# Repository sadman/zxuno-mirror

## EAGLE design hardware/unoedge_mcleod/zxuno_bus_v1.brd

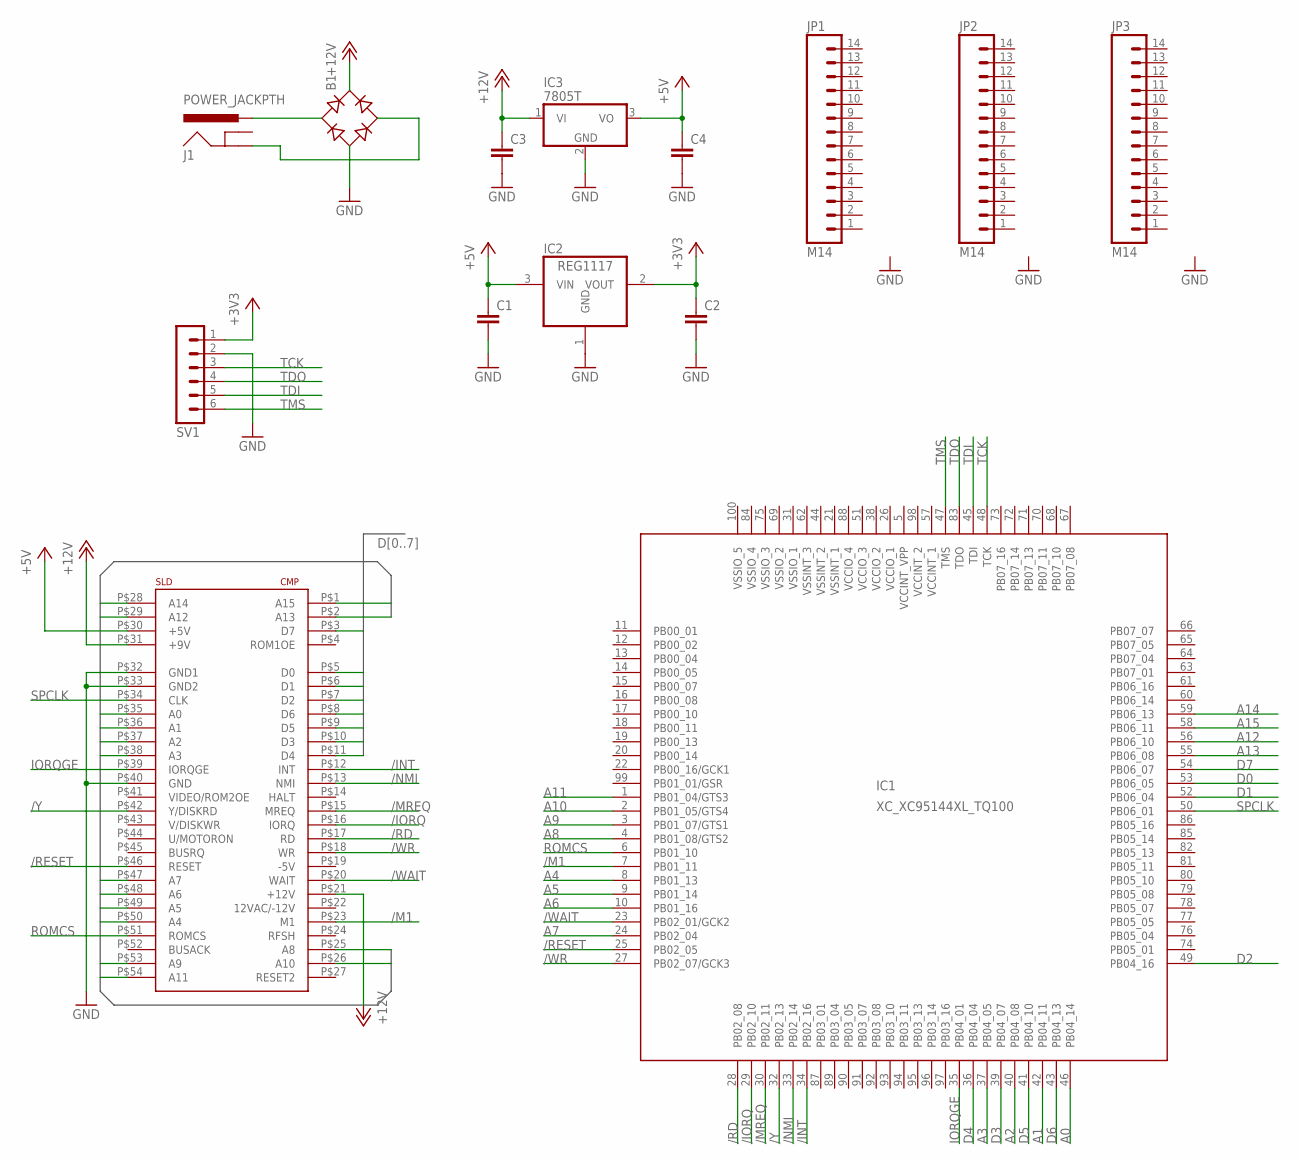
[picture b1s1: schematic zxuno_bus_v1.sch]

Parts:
B1: RB1A
C1, C2, C3, C4: C-EUC1206K; C1206K
IC1: XC_XC95144XL_TQ100; XC_XC-TQ100
IC2: REG1117; SOT223
IC3: 7805T; TO220H
J1: POWER_JACKPTH; POWER_JACK_PTH
JP1, JP2, JP3: M14; 1X14
SV1: MA06-1
U$1: CONECTOR_EDGE_LADO_SPECTRUM; CONECTOR_LADO_SPECTRUM

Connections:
+3V3: C2.1, IC1.5 (VCCINT_VPP), IC1.26 (VCCIO_1), IC1.38 (VCCIO_2), IC1.51 (VCCIO_3), IC1.57 (VCCINT_1), IC1.88 (VCCIO_4), IC1.98 (VCCINT_2), IC2.2 (VOUT), SV1.1
+5V: C1.1, C4.1, IC2.3 (VIN), IC3.3 (VO), U$1.P$30 (+5V)
+12V: B1.+, C3.1, IC3.1 (VI), U$1.P$21 (+12V), U$1.P$31 (+9V)
/INT: IC1.34 (PB02_16), U$1.P$12 (INT)
/IORQ: IC1.29 (PB02_10), U$1.P$16 (IORQ)
/M1: IC1.7 (PB01_11), U$1.P$23 (M1)
/MREQ: IC1.30 (PB02_11), U$1.P$15 (MREQ)
/NMI: IC1.33 (PB02_14), U$1.P$13 (NMI)
/RD: IC1.28 (PB02_08), U$1.P$17 (RD)
/RESET: IC1.25 (PB02_05), U$1.P$46 (RESET)
/WAIT: IC1.23 (PB02_01/GCK2), U$1.P$20 (WAIT)
/WR: IC1.27 (PB02_07/GCK3), U$1.P$18 (WR)
/Y: IC1.32 (PB02_13), U$1.P$42 (Y/DISKRD)
A0: IC1.46 (PB04_14), U$1.P$35 (A0)
A1: IC1.42 (PB04_11), U$1.P$36 (A1)
A2: IC1.40 (PB04_08), U$1.P$37 (A2)
A3: IC1.37 (PB04_05), U$1.P$38 (A3)
A4: IC1.8 (PB01_13), U$1.P$50 (A4)
A5: IC1.9 (PB01_14), U$1.P$49 (A5)
A6: IC1.10 (PB01_16), U$1.P$48 (A6)
A7: IC1.24 (PB02_04), U$1.P$47 (A7)
A8: IC1.4 (PB01_08/GTS2), U$1.P$25 (A8)
A9: IC1.3 (PB01_07/GTS1), U$1.P$53 (A9)
A10: IC1.2 (PB01_05/GTS4), U$1.P$26 (A10)
A11: IC1.1 (PB01_04/GTS3), U$1.P$54 (A11)
A12: IC1.56 (PB06_10), U$1.P$29 (A12)
A13: IC1.55 (PB06_08), U$1.P$2 (A13)
A14: IC1.59 (PB06_13), U$1.P$28 (A14)
A15: IC1.58 (PB06_11), U$1.P$1 (A15)
D0: IC1.53 (PB06_05), U$1.P$5 (D0)
D1: IC1.52 (PB06_04), U$1.P$6 (D1)
D2: IC1.49 (PB04_16), U$1.P$7 (D2)
D3: IC1.39 (PB04_07), U$1.P$10 (D3)
D4: IC1.36 (PB04_04), U$1.P$11 (D4)
D5: IC1.41 (PB04_10), U$1.P$9 (D5)
D6: IC1.43 (PB04_13), U$1.P$8 (D6)
D7: IC1.54 (PB06_07), U$1.P$3 (D7)
GND: B1.-, C1.2, C2.2, C3.2, C4.2, IC1.21 (VSSINT_1), IC1.31 (VSSIO_1), IC1.44 (VSSINT_2), IC1.62 (VSSINT_3), IC1.69 (VSSIO_2), IC1.75 (VSSIO_3), IC1.84 (VSSIO_4), IC1.100 (VSSIO_5), IC2.1 (GND), IC3.2 (GND), SV1.2, U$1.P$32 (GND1), U$1.P$33 (GND2), U$1.P$40 (GND)
IORQGE: IC1.35 (PB04_01), U$1.P$39 (IORQGE)
unnamed: B1.AC1, J1.PWR
unnamed: B1.AC2, J1.GND
ROMCS: IC1.6 (PB01_10), U$1.P$51 (ROMCS)
SPCLK: IC1.50 (PB06_01), U$1.P$34 (CLK)
TCK: IC1.48 (TCK), SV1.3
TDI: IC1.45 (TDI), SV1.5
TDO: IC1.83 (TDO), SV1.4
TMS: IC1.47 (TMS), SV1.6

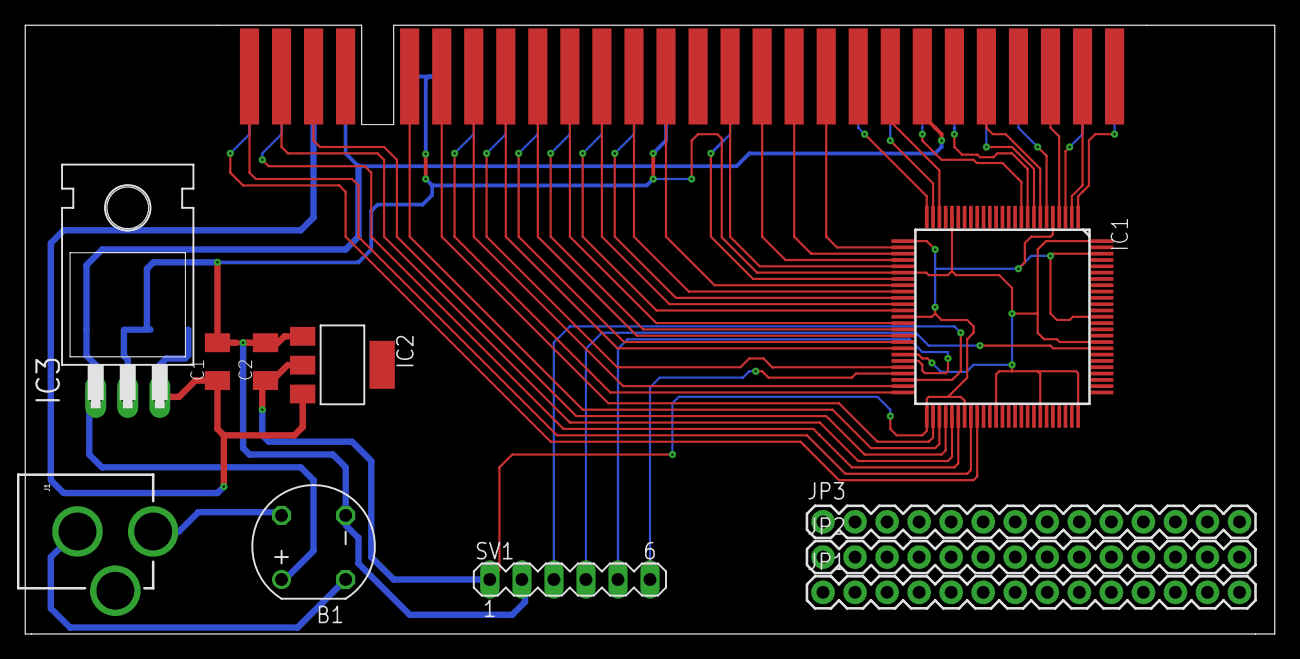
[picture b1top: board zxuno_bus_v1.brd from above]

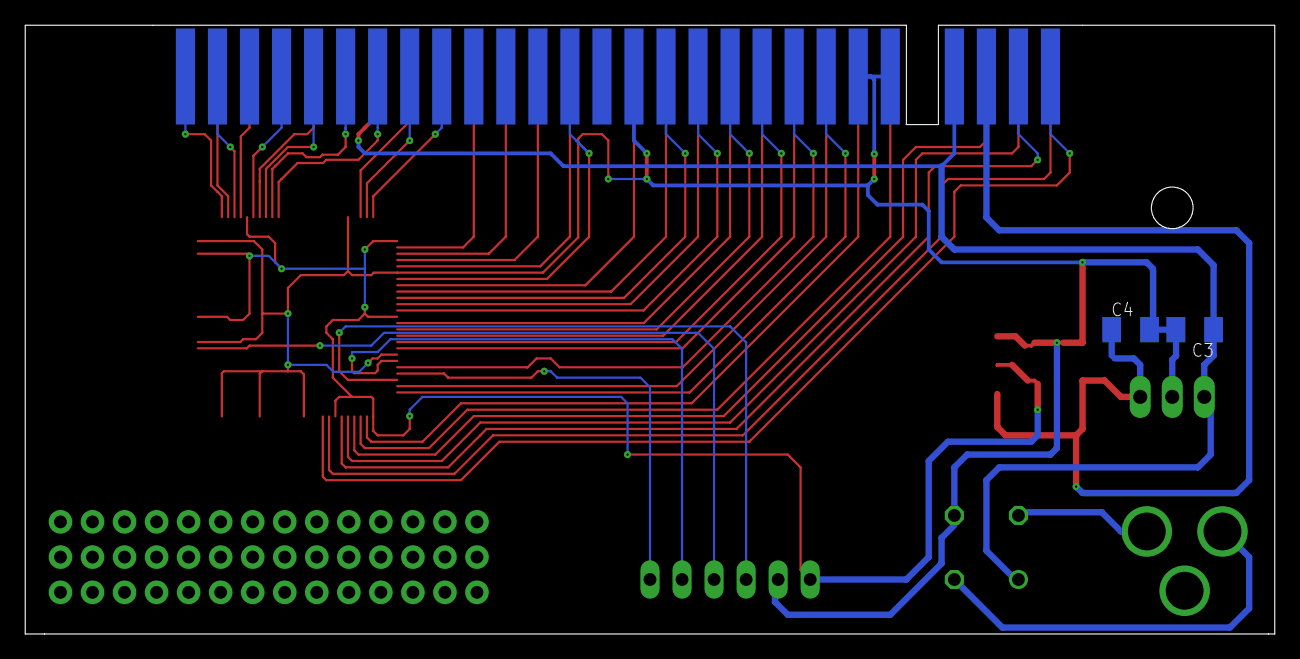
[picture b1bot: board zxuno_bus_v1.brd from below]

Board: 2 copper layers, 99.1 x 48.3 mm, 14 parts (2 on the bottom side), 47 nets.

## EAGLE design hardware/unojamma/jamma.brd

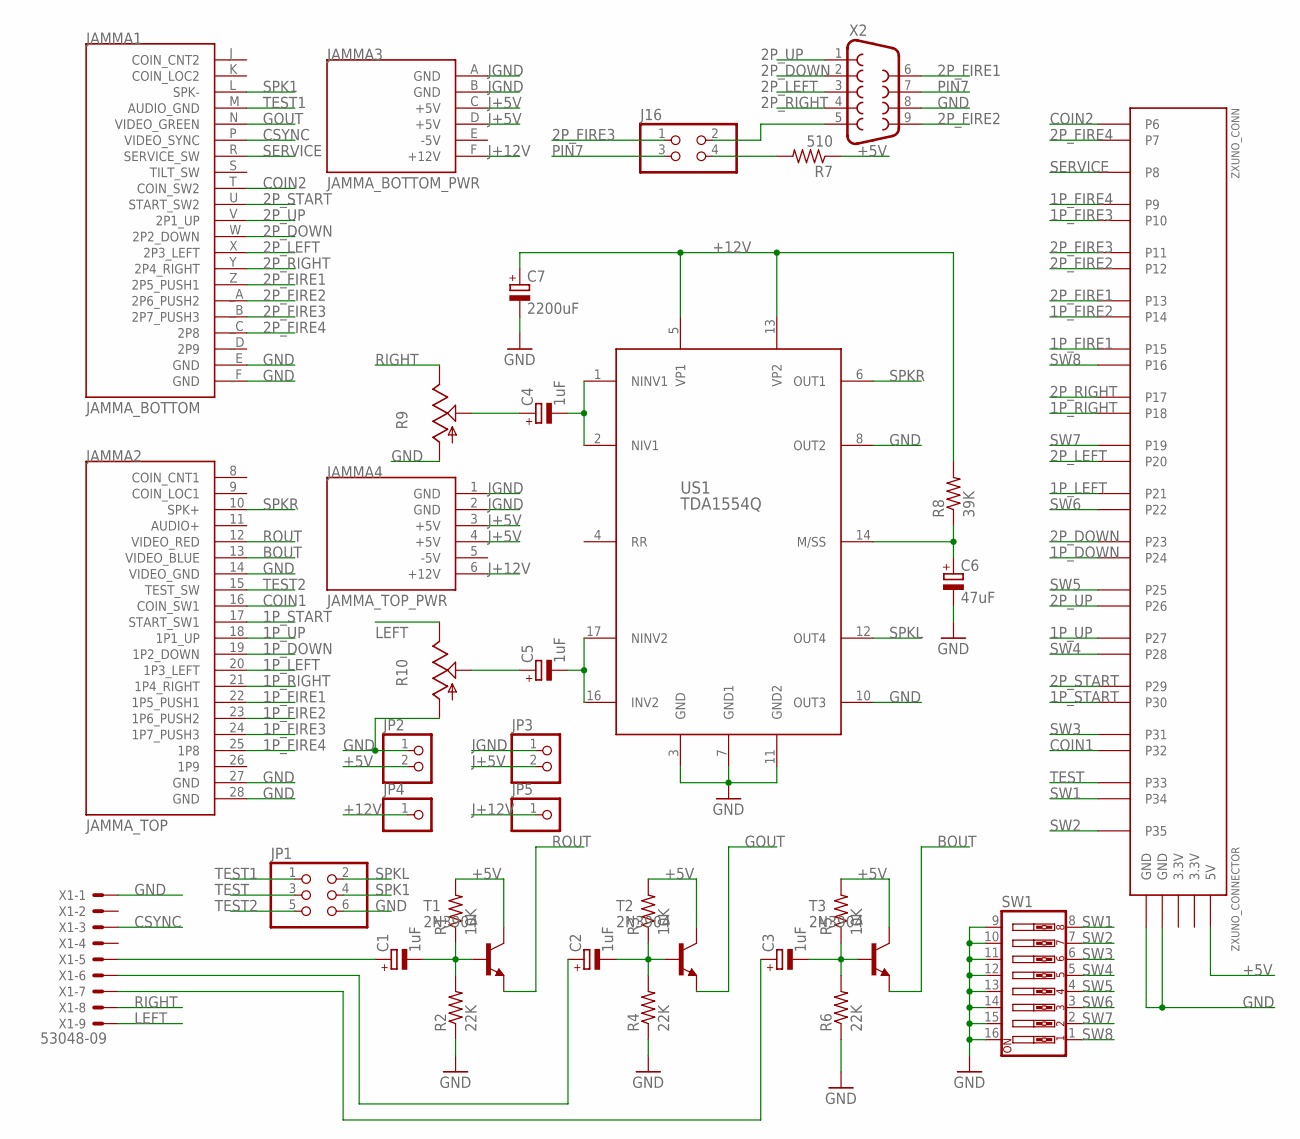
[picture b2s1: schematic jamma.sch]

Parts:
C1, C2, C3, C4, C5: 1uF; E2-5
C6: 47uF; E5-5
C7: 2200uF; E5-10,5
J16: PINHD-2X2; 2X02
JAMMA1: JAMMA_BOTTOM
JAMMA2: JAMMA_TOP
JAMMA3: JAMMA_BOTTOM_PWR
JAMMA4: JAMMA_TOP_PWR
JP1: PINHD-2X3/90; 2X03/90
JP2, JP3: PINHD-1X2; 1X02
JP4, JP5: PINHD-1X1; 1X01
R1, R3, R5: 10K; 0204/7
R2, R4, R6: 22K; 0204/7
R7: 510; 0204/7
R8: 39K; 0204/7
R9, R10: TRIM_US-CA6V; CA6V
SW1: SW_DIP-8; EDG-08
T1, T2, T3: 2N3904; TO92
US1: TDA1554Q; SOT243-1
X1: 53048-09
X2: DB9MALE; DB9_MALE
ZXUNO_CONN: ZXUNO_CONNECTOR

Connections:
1P_DOWN: JAMMA2.19 (1P2_DOWN), ZXUNO_CONN.P24
1P_FIRE1: JAMMA2.22 (1P5_PUSH1), ZXUNO_CONN.P15
1P_FIRE2: JAMMA2.23 (1P6_PUSH2), ZXUNO_CONN.P14
1P_FIRE3: JAMMA2.24 (1P7_PUSH3), ZXUNO_CONN.P10
1P_FIRE4: JAMMA2.25 (1P8), ZXUNO_CONN.P9
1P_LEFT: JAMMA2.20 (1P3_LEFT), ZXUNO_CONN.P21
1P_RIGHT: JAMMA2.21 (1P4_RIGHT), ZXUNO_CONN.P18
1P_START: JAMMA2.17 (START_SW1), ZXUNO_CONN.P30
1P_UP: JAMMA2.18 (1P1_UP), ZXUNO_CONN.P27
2P_DOWN: JAMMA1.W (2P2_DOWN), X2.2, ZXUNO_CONN.P23
2P_FIRE1: JAMMA1.Z (2P5_PUSH1), X2.6, ZXUNO_CONN.P13
2P_FIRE2: JAMMA1._A (2P6_PUSH2), X2.9, ZXUNO_CONN.P12
2P_FIRE3: J16.1, JAMMA1._B (2P7_PUSH3), ZXUNO_CONN.P11
2P_FIRE4: JAMMA1._C (2P8), ZXUNO_CONN.P7
2P_LEFT: JAMMA1.X (2P3_LEFT), X2.3, ZXUNO_CONN.P20
2P_RIGHT: JAMMA1.Y (2P4_RIGHT), X2.4, ZXUNO_CONN.P17
2P_START: JAMMA1.U (START_SW2), ZXUNO_CONN.P29
2P_UP: JAMMA1.V (2P1_UP), X2.1, ZXUNO_CONN.P26
3.3V: ZXUNO_CONN.3.3V@1 (3.3V), ZXUNO_CONN.3.3V@2 (3.3V)
+5V: JP2.2, R1.2, R3.2, R5.2, R7.1, T1.1 (C), T2.1 (C), T3.1 (C), ZXUNO_CONN.5V
+12V: C7.+, JP4.1, R8.2, US1.5 (VP1), US1.13 (VP2)
-5V: JAMMA3.E (-5V), JAMMA4.5 (-5V)
BIN: C3.+, X1.3
BOUT: JAMMA2.13 (VIDEO_BLUE), T3.3 (E)
COIN1: JAMMA2.16 (COIN_SW1), ZXUNO_CONN.P32
COIN2: JAMMA1.T (COIN_SW2), ZXUNO_CONN.P6
CSYNC: JAMMA1.P (VIDEO_SYNC), X1.7
GIN: C2.+, X1.4
GND: C6.-, C7.-, JAMMA1._E (GND), JAMMA1._F (GND), JAMMA2.14 (VIDEO_GND), JAMMA2.27 (GND), JAMMA2.28 (GND), JP1.6, JP2.1, R2.1, R4.1, R6.1, R9.A, R10.A, SW1.9, SW1.10, SW1.11, SW1.12, SW1.13, SW1.14, SW1.15, SW1.16, US1.3 (GND), US1.7 (GND1), US1.8 (OUT2), US1.10 (OUT3), US1.11 (GND2), X1.9, X2.8, ZXUNO_CONN.GND@1 (GND), ZXUNO_CONN.GND@2 (GND)
GOUT: JAMMA1.N (VIDEO_GREEN), T2.3 (E)
J+5V: JAMMA3.C (+5V), JAMMA3.D (+5V), JAMMA4.3 (+5V), JAMMA4.4 (+5V), JP3.2
J+12V: JAMMA3.F (+12V), JAMMA4.6 (+12V), JP5.1
JGND: JAMMA3.A (GND), JAMMA3.B (GND), JAMMA4.1 (GND), JAMMA4.2 (GND), JP3.1
LEFT: R10.E, X1.1
unnamed: C4.-, US1.1 (NINV1), US1.2 (NIV1)
unnamed: C5.-, US1.16 (INV2), US1.17 (NINV2)
unnamed: C5.+, R10.S
unnamed: C1.-, R1.1, R2.2, T1.2 (B)
unnamed: J16.2, X2.5
unnamed: C6.+, R8.1, US1.14 (M/SS)
unnamed: C3.-, R5.1, R6.2, T3.2 (B)
unnamed: C4.+, R9.S
unnamed: C2.-, R3.1, R4.2, T2.2 (B)
unnamed: J16.4, R7.2
PIN7: J16.3, X2.7
RIGHT: R9.E, X1.2
RIN: C1.+, X1.5
ROUT: JAMMA2.12 (VIDEO_RED), T1.3 (E)
SERVICE: JAMMA1.R (SERVICE_SW), ZXUNO_CONN.P8
SPK1: JAMMA1.L (SPK-), JP1.4
SPKL: JP1.2, US1.12 (OUT4)
SPKR: JAMMA2.10 (SPK+), US1.6 (OUT1)
SW1: SW1.8, ZXUNO_CONN.P34
SW2: SW1.7, ZXUNO_CONN.P35
SW3: SW1.6, ZXUNO_CONN.P31
SW4: SW1.5, ZXUNO_CONN.P28
SW5: SW1.4, ZXUNO_CONN.P25
SW6: SW1.3, ZXUNO_CONN.P22
SW7: SW1.2, ZXUNO_CONN.P19
SW8: SW1.1, ZXUNO_CONN.P16
TEST: JP1.3, ZXUNO_CONN.P33
TEST1: JAMMA1.M (AUDIO_GND), JP1.1
TEST2: JAMMA2.15 (TEST_SW), JP1.5

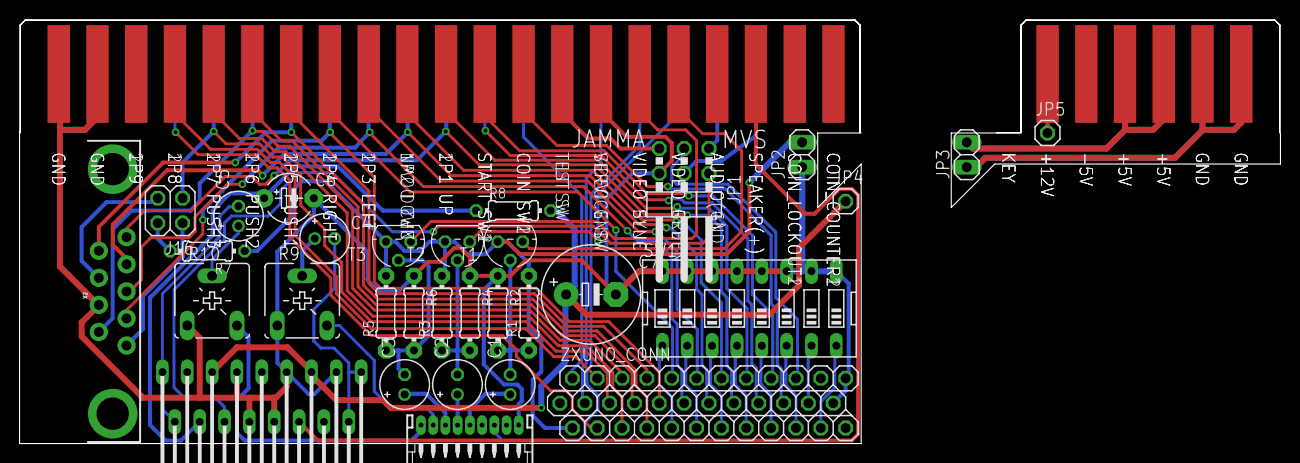
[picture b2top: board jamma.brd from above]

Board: 2 copper layers, 128.9 x 43.3 mm, 35 parts (0 on the bottom side), 63 nets.

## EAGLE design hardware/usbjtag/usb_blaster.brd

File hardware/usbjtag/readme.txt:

Schematics and firmware source code here:
http://sa89a.net/mp.cgi/ele/ub.htm

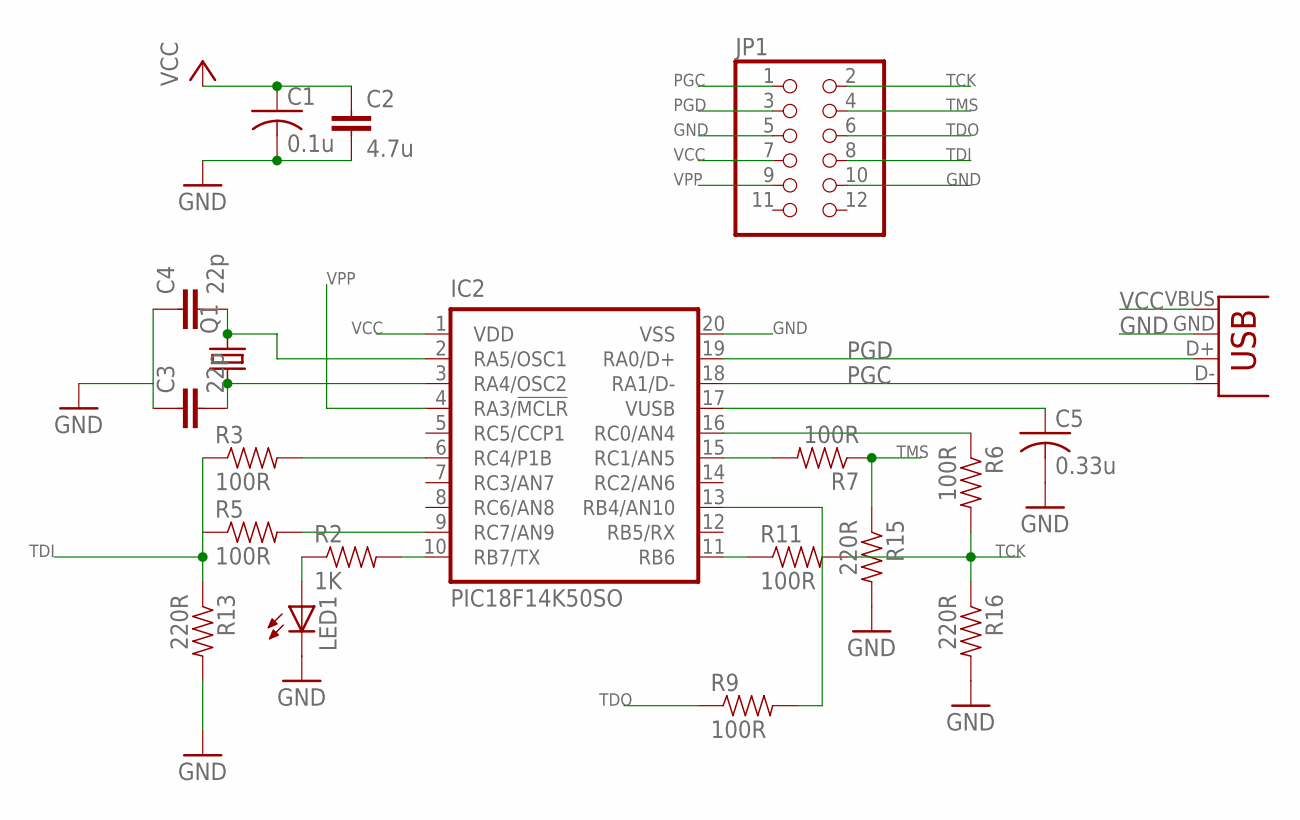
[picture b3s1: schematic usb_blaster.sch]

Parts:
C1: 0.1u; C0603K
C2: 4.7u; 0805
C3, C4: 22p; 0805
C5: 0.33u; C0603K
IC2: PIC18F14K50SO; SO20
JP1: PINHD-2X6; 2X06
LED1: LEDCHIP-LED0805; CHIP-LED0805
Q1: CRYSTALHC49UP; HC49UP
R2: 1K; 0805
R3, R5, R6, R7, R9, R11: 100R; 0805
R13, R15, R16: 220R; 0805
X2: USB-A-H

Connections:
GND: C1.2, C2.2, C3.1, C4.1, C5.2, IC2.20 (VSS), JP1.5, JP1.10, LED1.C, R13.2, R15.2, R16.2, X2.GND (VBUS)
unnamed: C4.2, IC2.2 (RA5/OSC1), Q1.2
unnamed: IC2.15 (RC1/AN5), R7.2
unnamed: C3.2, IC2.3 (RA4/OSC2), Q1.1
unnamed: IC2.16 (RC0/AN4), R6.1
unnamed: IC2.13 (RB4/AN10), R9.2
unnamed: IC2.6 (RC4/P1B), R3.2
unnamed: C5.1, IC2.17 (VUSB)
unnamed: IC2.9 (RC7/AN9), R5.2
unnamed: IC2.10 (RB7/TX), R2.2
unnamed: LED1.A, R2.1
unnamed: IC2.11 (RB6), R11.1
PGC: IC2.18 (RA1/D-), JP1.1, X2.D- (D+)
PGD: IC2.19 (RA0/D+), JP1.3, X2.D+ (D-)
TCK: JP1.2, R6.2, R11.2, R16.1
TDI: JP1.8, R3.1, R5.1, R13.1
TDO: JP1.6, R9.1
TMS: JP1.4, R7.1, R15.1
VCC: C1.1, C2.1, IC2.1 (VDD), JP1.7, X2.VBUS (GND)
VPP: IC2.4 (RA3/!MCLR!), JP1.9

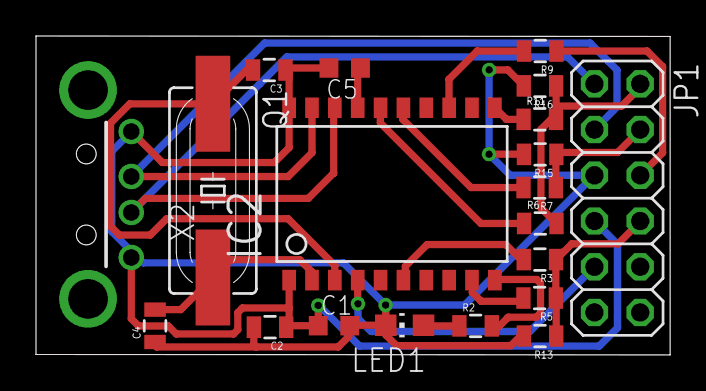
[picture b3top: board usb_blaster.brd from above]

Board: 2 copper layers, 35.2 x 17.7 mm, 20 parts (0 on the bottom side), 20 nets.

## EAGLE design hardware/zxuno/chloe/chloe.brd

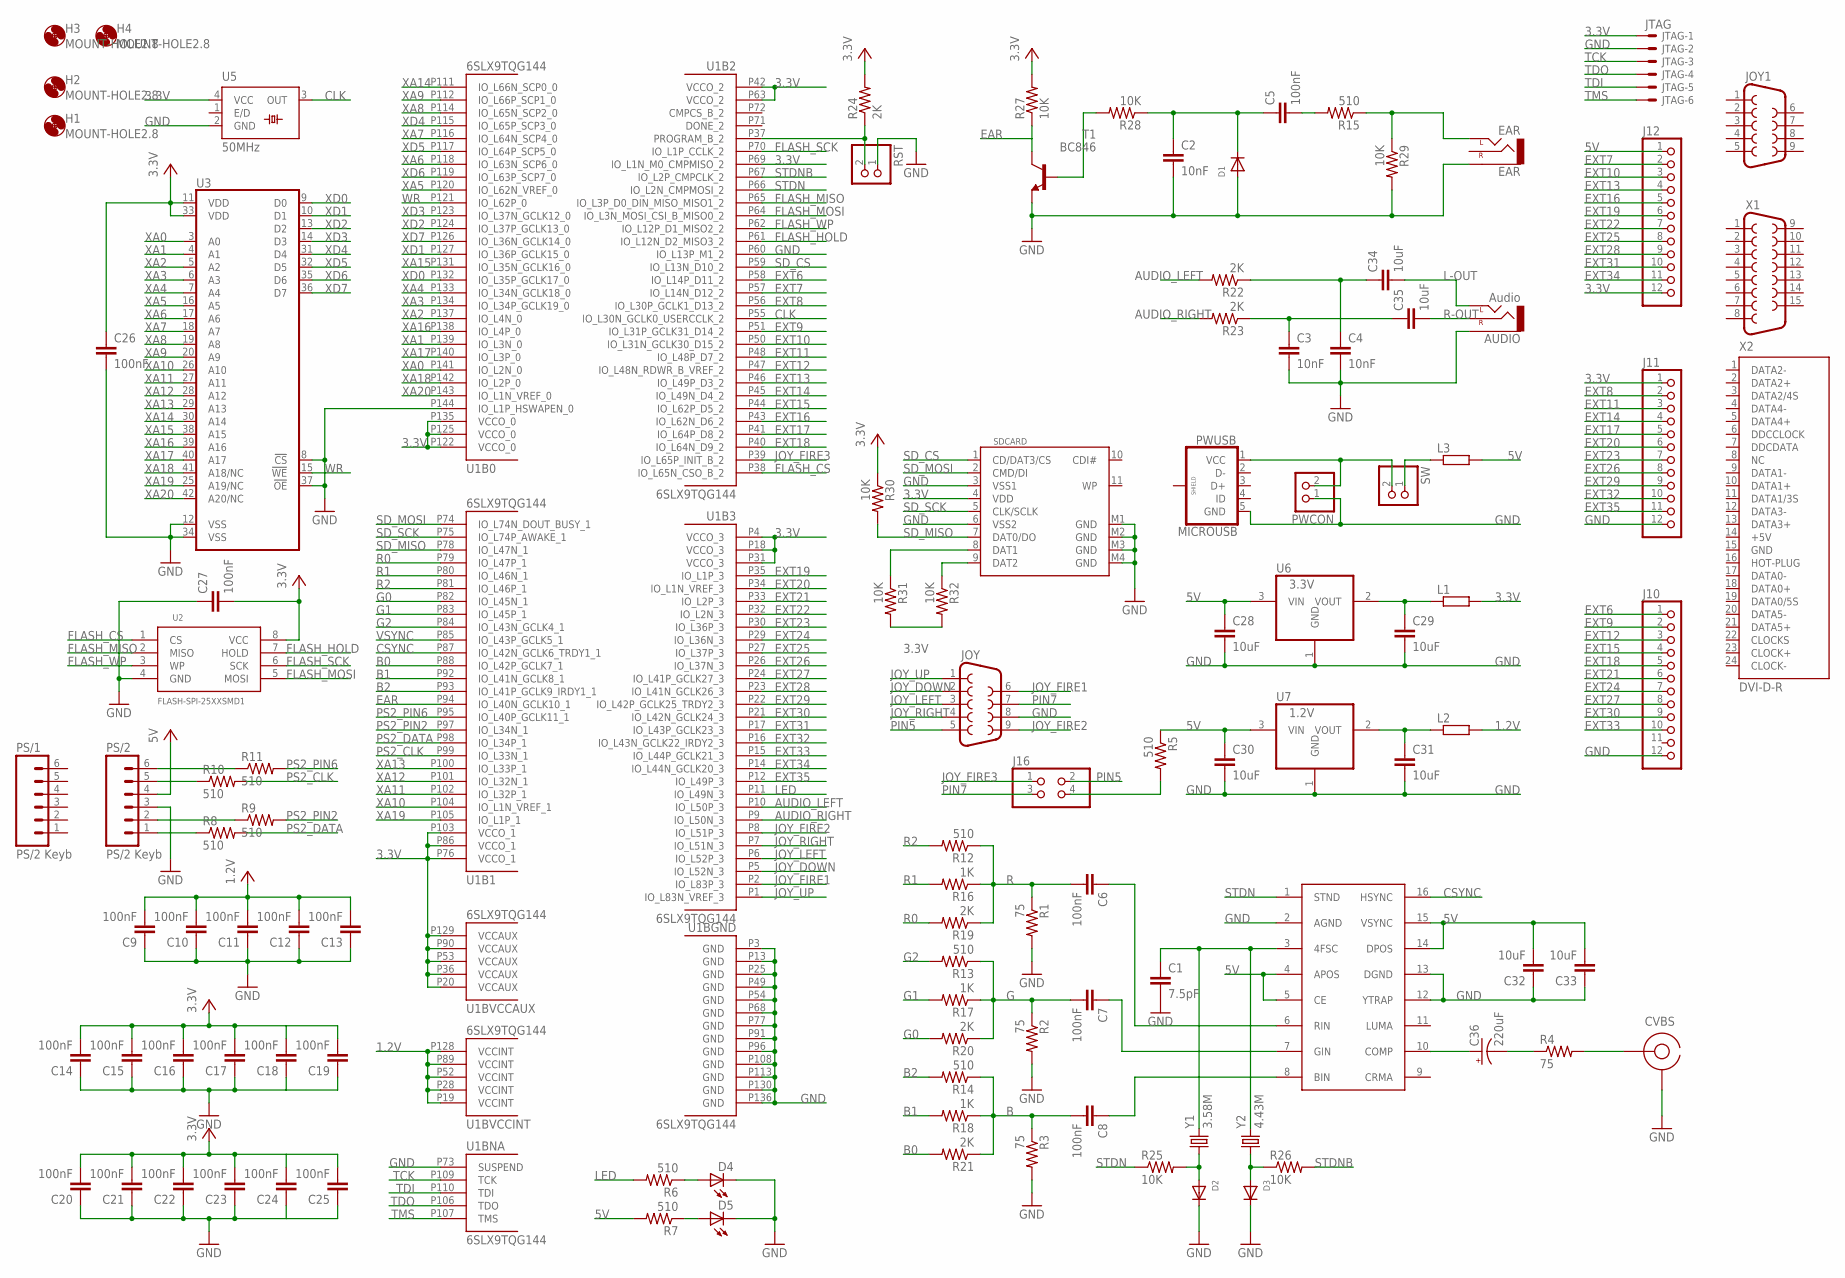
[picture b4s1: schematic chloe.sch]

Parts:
AUDIO: Audio; AUDIO-JACK
C1: 7.5pF; C0805
C2, C3, C4: 10nF; C0805
C5, C6, C7, C8, C9, C10, C11, C12, C13, C14, C15, C16, C17, C18, C19, C20, C21, C22, C23, C24, C25, C26, C27: 100nF; C0603
C28, C29, C30, C31, C32, C33, C34, C35: 10uF; C0805
C36: 220uF; 153CLV-0605
CVBS: RCA
D1, D2, D3: DIODESOD-323F; SOD-323F
D4, D5: LEDCHIP-LED0805; CHIP-LED0805
EAR: EAR; AUDIO-JACK
H1, H2, H3, H4: MOUNT-HOLE2.8; 2,8
J10, J11, J12: PINHD-1X12; 1X12
J16: PINHD-2X2; 2X02
JOY, JOY1: DB9MALE; DB9_MALE
JTAG: JTAG; 53047-06
L1, L2, L3: R-EU_M0805; M0805
PS/1, PS/2: PS/2 Keyb; DINC/MIN_TM/6_1PRIMARY
PWCON: PINHD-1X2; 1X02
PWUSB: MICROUSB; MICRO_USB_1PRIMARY
R1, R2, R3, R4: 75; M0805
R5, R6, R7, R8, R9, R10, R11, R12, R13, R14, R15: 510; M0805
R16, R17, R18: 1K; M0805
R19, R20, R21, R22, R23, R24: 2K; M0805
R25, R26, R27, R28, R29, R30, R31, R32: 10K; M0805
RST: PINHD-1X2; 1X02
SDCARD: SDCARD; SDCMF-10915W010
SW: PINHD-1X2; 1X02
T1: BC846; SOT23
U1: 6SLX9TQG144; TQ144
U2: FLASH-SPI-25XXSMD1; SO08-EIAJ
U3: ISSI_SRAM_8BIT; TSOP44-II
U4: AD724; SO16W
U5: 50MHz; SM/OSC_1PRIMARY
U6: 3.3V; SOT223
U7: 1.2V; SOT223
X1: F15HDH; HDF15H
X2: DVI-D-R
Y1: 3.58M; HC49UP
Y2: 4.43M; HC49UP

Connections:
1.2V: C9.2, C10.2, C11.2, C12.2, C13.2, L2.2, U1.P19 (VCCINT), U1.P28 (VCCINT), U1.P52 (VCCINT), U1.P89 (VCCINT), U1.P128 (VCCINT)
3.3V: C14.2, C15.2, C16.2, C17.2, C18.2, C19.2, C20.2, C21.2, C22.2, C23.2, C24.2, C25.2, C26.1, C27.2, J11.1, J12.12, JTAG.1, L1.2, R24.2, R27.2, R30.1, R31.2, R32.2, SDCARD.4 (VDD), U1.P4 (VCCO_3), U1.P18 (VCCO_3), U1.P20 (VCCAUX), U1.P31 (VCCO_3), U1.P36 (VCCAUX), U1.P42 (VCCO_2), U1.P53 (VCCAUX), U1.P63 (VCCO_2), U1.P69 (IO_L1N_M0_CMPMISO_2), U1.P76 (VCCO_1), U1.P86 (VCCO_1), U1.P90 (VCCAUX), U1.P103 (VCCO_1), U1.P122 (VCCO_0), U1.P125 (VCCO_0), U1.P129 (VCCAUX), U1.P135 (VCCO_0), U2.8 (VCC), U3.11 (VDD), U3.33 (VDD), U5.4 (VCC)
5V: C28.1, C30.1, C32.2, C33.2, J12.1, L3.2, PS/2.4, R5.1, R7.2, U4.4 (APOS), U4.5 (CE), U4.14 (DPOS), U4.15 (VSYNC), U6.3 (VIN), U7.3 (VIN)
+5V: X2.14 (+5V)
AUDIO_LEFT: R22.2, U1.P10 (IO_L50P_3)
AUDIO_RIGHT: R23.2, U1.P9 (IO_L50N_3)
B: C8.2, R3.1, R14.1, R18.1, R21.1
B0: R21.2, U1.P88 (IO_L42P_GCLK7_1)
B1: R18.2, U1.P92 (IO_L41N_GCLK8_1)
B2: R14.2, U1.P93 (IO_L41P_GCLK9_IRDY1_1)
CLK: U1.P55 (IO_L30N_GCLK0_USERCCLK_2), U5.3 (OUT)
CSYNC: U1.P87 (IO_L42N_GCLK6_TRDY1_1), U4.16 (HSYNC)
EAR: R27.1, T1.3 (C), U1.P94 (IO_L40N_GCLK10_1)
EXT6: J10.1, U1.P58 (IO_L14P_D11_2)
EXT7: J12.2, U1.P57 (IO_L14N_D12_2)
EXT8: J11.2, U1.P56 (IO_L30P_GCLK1_D13_2)
EXT9: J10.2, U1.P51 (IO_L31P_GCLK31_D14_2)
EXT10: J12.3, U1.P50 (IO_L31N_GCLK30_D15_2)
EXT11: J11.3, U1.P48 (IO_L48P_D7_2)
EXT12: J10.3, U1.P47 (IO_L48N_RDWR_B_VREF_2)
EXT13: J12.4, U1.P46 (IO_L49P_D3_2)
EXT14: J11.4, U1.P45 (IO_L49N_D4_2)
EXT15: J10.4, U1.P44 (IO_L62P_D5_2)
EXT16: J12.5, U1.P43 (IO_L62N_D6_2)
EXT17: J11.5, U1.P41 (IO_L64P_D8_2)
EXT18: J10.5, U1.P40 (IO_L64N_D9_2)
EXT19: J12.6, U1.P35 (IO_L1P_3)
EXT20: J11.6, U1.P34 (IO_L1N_VREF_3)
EXT21: J10.6, U1.P33 (IO_L2P_3)
EXT22: J12.7, U1.P32 (IO_L2N_3)
EXT23: J11.7, U1.P30 (IO_L36P_3)
EXT24: J10.7, U1.P29 (IO_L36N_3)
EXT25: J12.8, U1.P27 (IO_L37P_3)
EXT26: J11.8, U1.P26 (IO_L37N_3)
EXT27: J10.8, U1.P24 (IO_L41P_GCLK27_3)
EXT28: J12.9, U1.P23 (IO_L41N_GCLK26_3)
EXT29: J11.9, U1.P22 (IO_L42P_GCLK25_TRDY2_3)
EXT30: J10.9, U1.P21 (IO_L42N_GCLK24_3)
EXT31: J12.10, U1.P17 (IO_L43P_GCLK23_3)
EXT32: J11.10, U1.P16 (IO_L43N_GCLK22_IRDY2_3)
EXT33: J10.10, U1.P15 (IO_L44P_GCLK21_3)
EXT34: J12.11, U1.P14 (IO_L44N_GCLK20_3)
EXT35: J11.11, U1.P12 (IO_L49P_3)
FLASH_CS: U1.P38 (IO_L65N_CSO_B_2), U2.1 (CS)
FLASH_HOLD: U1.P61 (IO_L12N_D2_MISO3_2), U2.7 (HOLD)
FLASH_MISO: U1.P65 (IO_L3P_D0_DIN_MISO_MISO1_2), U2.2 (MISO)
FLASH_MOSI: U1.P64 (IO_L3N_MOSI_CSI_B_MISO0_2), U2.5 (MOSI)
FLASH_SCK: U1.P70 (IO_L1P_CCLK_2), U2.6 (SCK)
FLASH_WP: U1.P62 (IO_L12P_D1_MISO2_2), U2.3 (WP)
G: C7.2, R2.1, R13.1, R17.1, R20.1
G0: R20.2, U1.P82 (IO_L45N_1)
G1: R17.2, U1.P83 (IO_L45P_1)
G2: R13.2, U1.P84 (IO_L43N_GCLK4_1)
GND: AUDIO.SLEEVE, C1.2, C2.2, C3.2, C4.2, C9.1, C10.1, C11.1, C12.1, C13.1, C14.1, C15.1, C16.1, C17.1, C18.1, C19.1, C20.1, C21.1, C22.1, C23.1, C24.1, C25.1, C26.2, C27.1, C28.2, C29.2, C30.2, C31.2, C32.1, C33.1, CVBS.GND, D1.A, D2.C, D3.C, D4.C, D5.C, EAR.SLEEVE, J10.12, J11.12, JOY.8, JTAG.2, PS/2.3, PWCON.1, PWUSB.5 (GND), R1.2, R2.2, R3.2, R29.2, RST.1, SDCARD.3 (VSS1), SDCARD.6 (VSS2), SDCARD.M1 (GND), SDCARD.M2 (GND), SDCARD.M3 (GND), SDCARD.M4 (GND), T1.2 (E), U1.P3 (GND), U1.P13 (GND), U1.P25 (GND), U1.P49 (GND), U1.P54 (GND), U1.P60 (IO_L13P_M1_2), U1.P68 (GND), U1.P73 (SUSPEND), U1.P77 (GND), U1.P91 (GND), U1.P96 (GND), U1.P108 (GND), U1.P113 (GND), U1.P130 (GND), U1.P136 (GND), U1.P144 (IO_L1P_HSWAPEN_0), U2.4 (GND), U3.8 (!CS), U3.12 (VSS), U3.34 (VSS), U3.37 (!OE), U4.2 (AGND), U4.12 (YTRAP), U4.13 (DGND), U5.2 (GND), U6.1 (GND), U7.1 (GND), X2.15 (GND)
JOY_DOWN: JOY.2, U1.P5 (IO_L52N_3)
JOY_FIRE1: JOY.6, U1.P2 (IO_L83P_3)
JOY_FIRE2: JOY.9, U1.P8 (IO_L51P_3)
JOY_FIRE3: J16.1, U1.P39 (IO_L65P_INIT_B_2)
JOY_LEFT: JOY.3, U1.P6 (IO_L52P_3)
JOY_RIGHT: JOY.4, U1.P7 (IO_L51N_3)
JOY_UP: JOY.1, U1.P1 (IO_L83N_VREF_3)
L-OUT: AUDIO.TIP (LEFT), C34.2
LED: R6.2, U1.P11 (IO_L49N_3)
unnamed: PS/2.6, R11.1
unnamed: PS/2.5, R10.1
unnamed: PS/2.2, R9.1
unnamed: PS/2.1, R8.1
unnamed: R24.1, RST.2, U1.P37 (PROGRAM_B_2)
unnamed: R28.2, T1.1 (B)
unnamed: C2.1, C5.1, D1.C, R28.1
unnamed: C5.2, R15.2
unnamed: EAR.TIP (LEFT), R15.1, R29.1
unnamed: C3.1, C35.1, R23.1
unnamed: C4.1, C34.1, R22.1
unnamed: PWCON.2, PWUSB.1 (VCC), SW.2
unnamed: L3.1, SW.1
unnamed: C29.1, L1.1, U6.2 (VOUT)
unnamed: J16.4, R5.2
unnamed: C31.1, L2.1, U7.2 (VOUT)
unnamed: R31.1, SDCARD.8 (DAT1)
unnamed: C8.1, U4.8 (BIN)
unnamed: R32.1, SDCARD.9 (DAT2)
unnamed: C7.1, U4.7 (GIN)
unnamed: C6.1, U4.6 (RIN)
unnamed: C1.1, U4.3 (4FSC), Y1.2, Y2.2
unnamed: D3.A, R26.1, Y2.1
unnamed: D2.A, R25.2, Y1.1
unnamed: C36.+, U4.10 (COMP)
unnamed: C36.-, R4.1
unnamed: CVBS.SIG, R4.2
unnamed: D4.A, R6.1
unnamed: D5.A, R7.1
PIN5: J16.2, JOY.5
PIN7: J16.3, JOY.7
PS2_CLK: R10.2, U1.P99 (IO_L33N_1)
PS2_DATA: R8.2, U1.P98 (IO_L34P_1)
PS2_PIN2: R9.2, U1.P97 (IO_L34N_1)
PS2_PIN6: R11.2, U1.P95 (IO_L40P_GCLK11_1)
R: C6.2, R1.1, R12.1, R16.1, R19.1
R0: R19.2, U1.P79 (IO_L47P_1)
R1: R16.2, U1.P80 (IO_L46N_1)
R2: R12.2, U1.P81 (IO_L46P_1)
R-OUT: AUDIO.RING (RIGHT), C35.2
SD_CS: SDCARD.1 (CD/DAT3/CS), U1.P59 (IO_L13N_D10_2)
SD_MISO: R30.2, SDCARD.7 (DAT0/DO), U1.P78 (IO_L47N_1)
SD_MOSI: SDCARD.2 (CMD/DI), U1.P74 (IO_L74N_DOUT_BUSY_1)
SD_SCK: SDCARD.5 (CLK/SCLK), U1.P75 (IO_L74P_AWAKE_1)
STDN: R25.1, U1.P66 (IO_L2N_CMPMOSI_2), U4.1 (STND)
STDNB: R26.2, U1.P67 (IO_L2P_CMPCLK_2)
TCK: JTAG.3, U1.P109 (TCK)
TDI: JTAG.5, U1.P110 (TDI)
TDO: JTAG.4, U1.P106 (TDO)
TMS: JTAG.6, U1.P107 (TMS)
VSYNC: U1.P85 (IO_L43P_GCLK5_1)
WR: U1.P121 (IO_L62P_0), U3.15 (!WE)
XA0: U1.P141 (IO_L2N_0), U3.3 (A0)
XA1: U1.P139 (IO_L3N_0), U3.4 (A1)
XA2: U1.P137 (IO_L4N_0), U3.5 (A2)
XA3: U1.P134 (IO_L34P_GCLK19_0), U3.6 (A3)
XA4: U1.P133 (IO_L34N_GCLK18_0), U3.7 (A4)
XA5: U1.P120 (IO_L62N_VREF_0), U3.16 (A5)
XA6: U1.P118 (IO_L63N_SCP6_0), U3.17 (A6)
XA7: U1.P116 (IO_L64N_SCP4_0), U3.18 (A7)
XA8: U1.P114 (IO_L65N_SCP2_0), U3.19 (A8)
XA9: U1.P112 (IO_L66P_SCP1_0), U3.20 (A9)
XA10: U1.P104 (IO_L1N_VREF_1), U3.26 (A10)
XA11: U1.P102 (IO_L32P_1), U3.27 (A11)
XA12: U1.P101 (IO_L32N_1), U3.28 (A12)
XA13: U1.P100 (IO_L33P_1), U3.29 (A13)
XA14: U1.P111 (IO_L66N_SCP0_0), U3.30 (A14)
XA15: U1.P131 (IO_L35N_GCLK16_0), U3.38 (A15)
XA16: U1.P138 (IO_L4P_0), U3.39 (A16)
XA17: U1.P140 (IO_L3P_0), U3.40 (A17)
XA18: U1.P142 (IO_L2P_0), U3.41 (A18/NC)
XA19: U1.P105 (IO_L1P_1), U3.25 (A19/NC)
XA20: U1.P143 (IO_L1N_VREF_0), U3.42 (A20/NC)
XD0: U1.P132 (IO_L35P_GCLK17_0), U3.9 (D0)
XD1: U1.P127 (IO_L36P_GCLK15_0), U3.10 (D1)
XD2: U1.P124 (IO_L37P_GCLK13_0), U3.13 (D2)
XD3: U1.P123 (IO_L37N_GCLK12_0), U3.14 (D3)
XD4: U1.P115 (IO_L65P_SCP3_0), U3.31 (D4)
XD5: U1.P117 (IO_L64P_SCP5_0), U3.32 (D5)
XD6: U1.P119 (IO_L63P_SCP7_0), U3.35 (D6)
XD7: U1.P126 (IO_L36N_GCLK14_0), U3.36 (D7)

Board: 2 copper layers, 109 parts (21 on the bottom side), 142 nets, no tracks yet.

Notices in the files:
hardware/zxuno/chloe/chloe.brd:
(C)2016 ZX-Uno Team
parts and their libraries:
SparkFun-Connectors: Licensing: Creative Commons ShareAlike 4.0 International - https://creativecommons.org/licenses/by-sa/4.0
